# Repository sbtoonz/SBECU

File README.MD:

Original design sourced from https://github.com/dvjcodec/SCG-ECU-1.0
Teensy schematic sourced from PJRC

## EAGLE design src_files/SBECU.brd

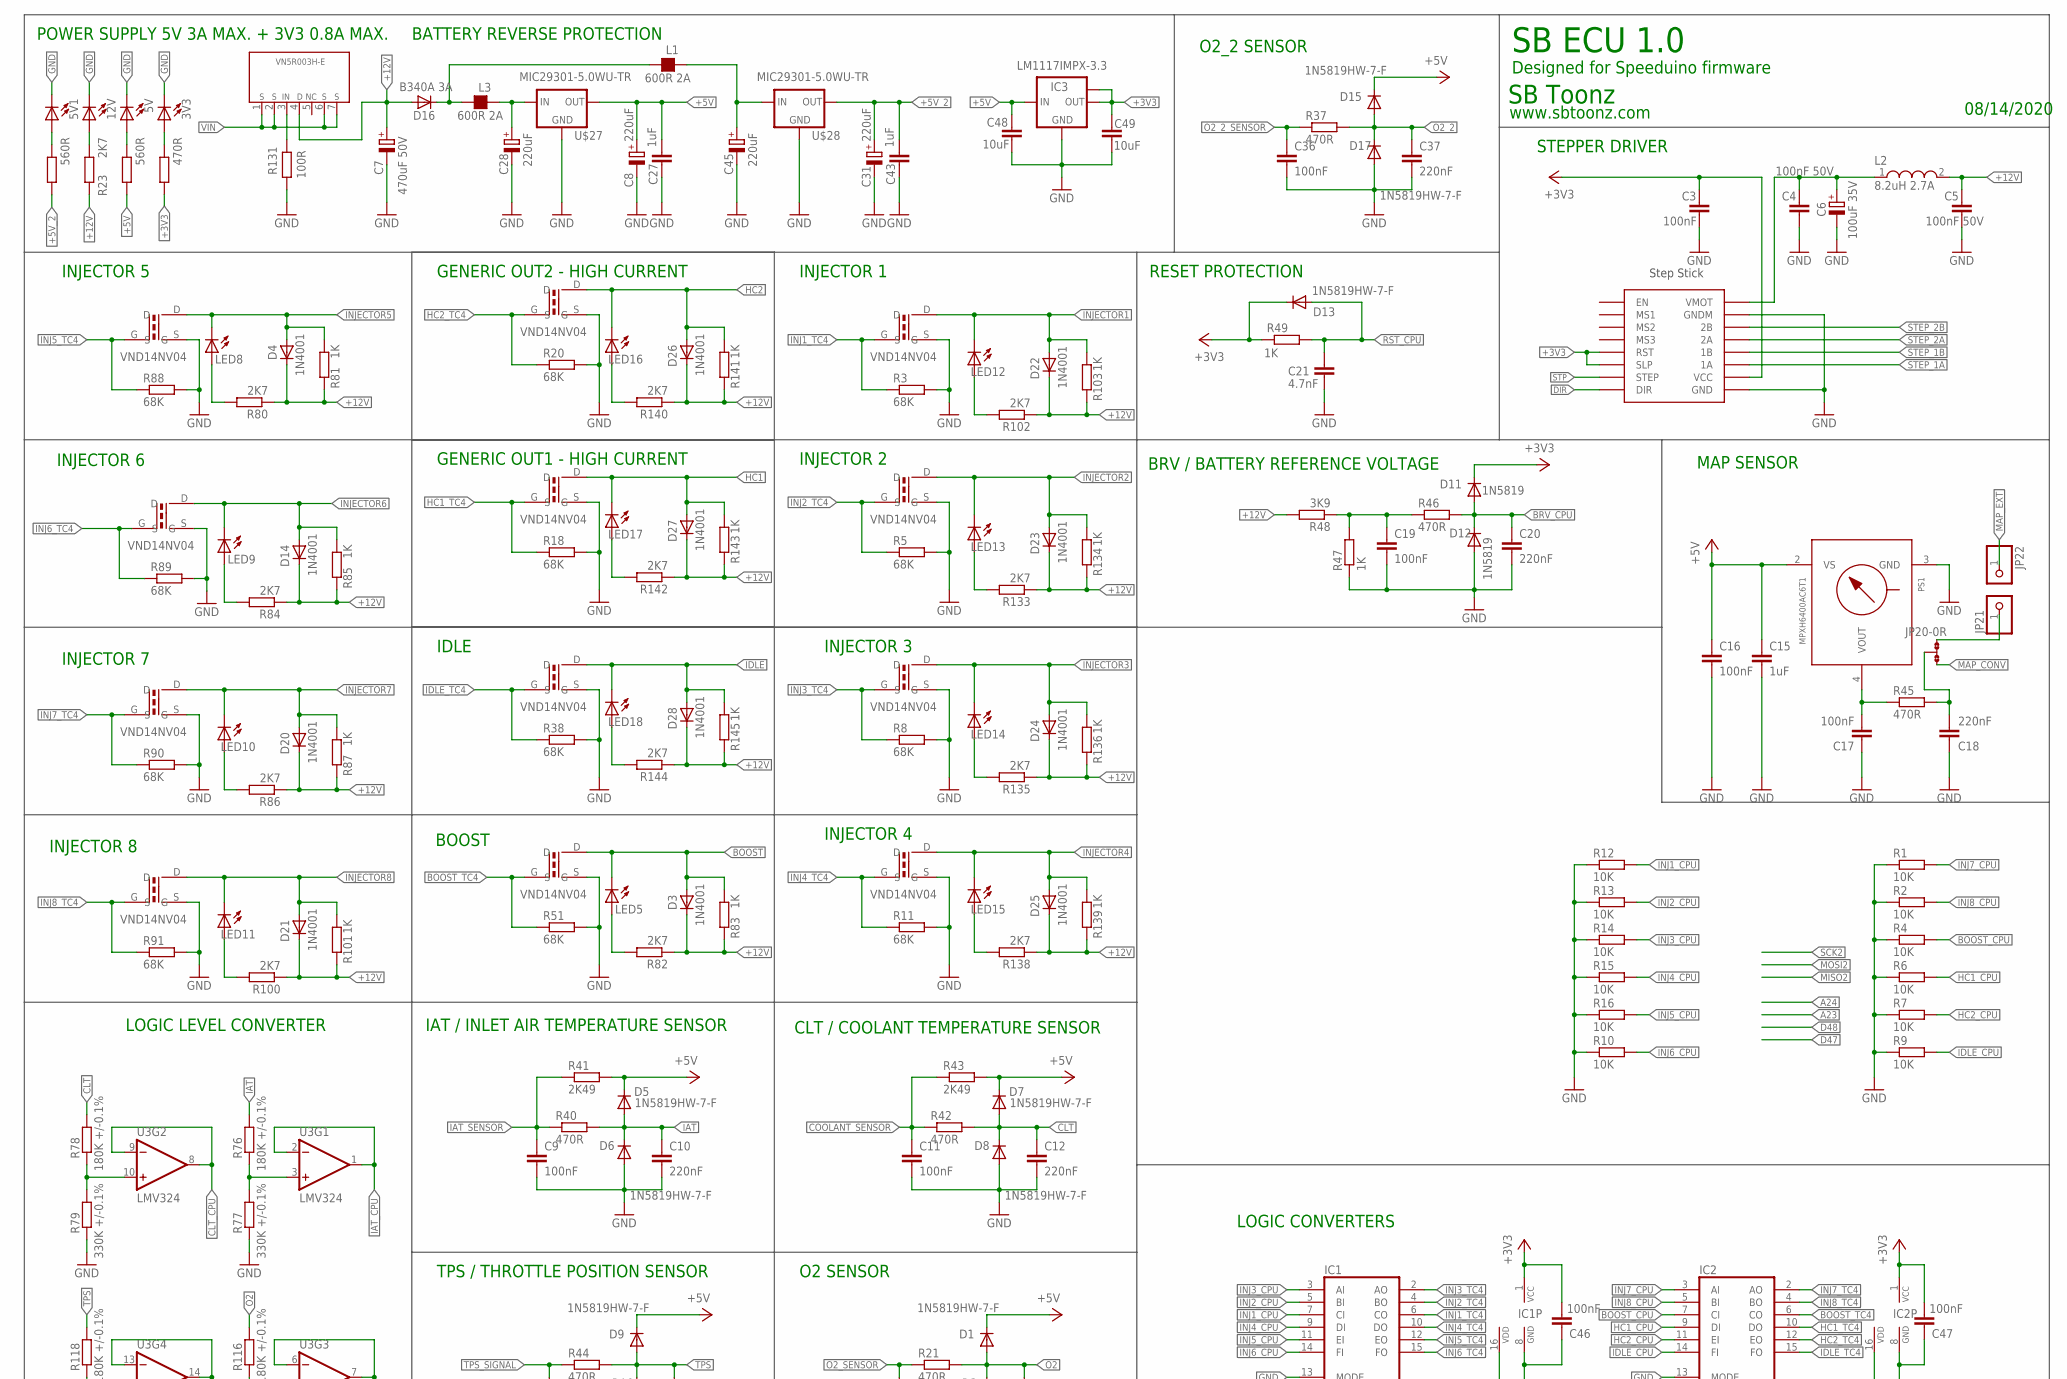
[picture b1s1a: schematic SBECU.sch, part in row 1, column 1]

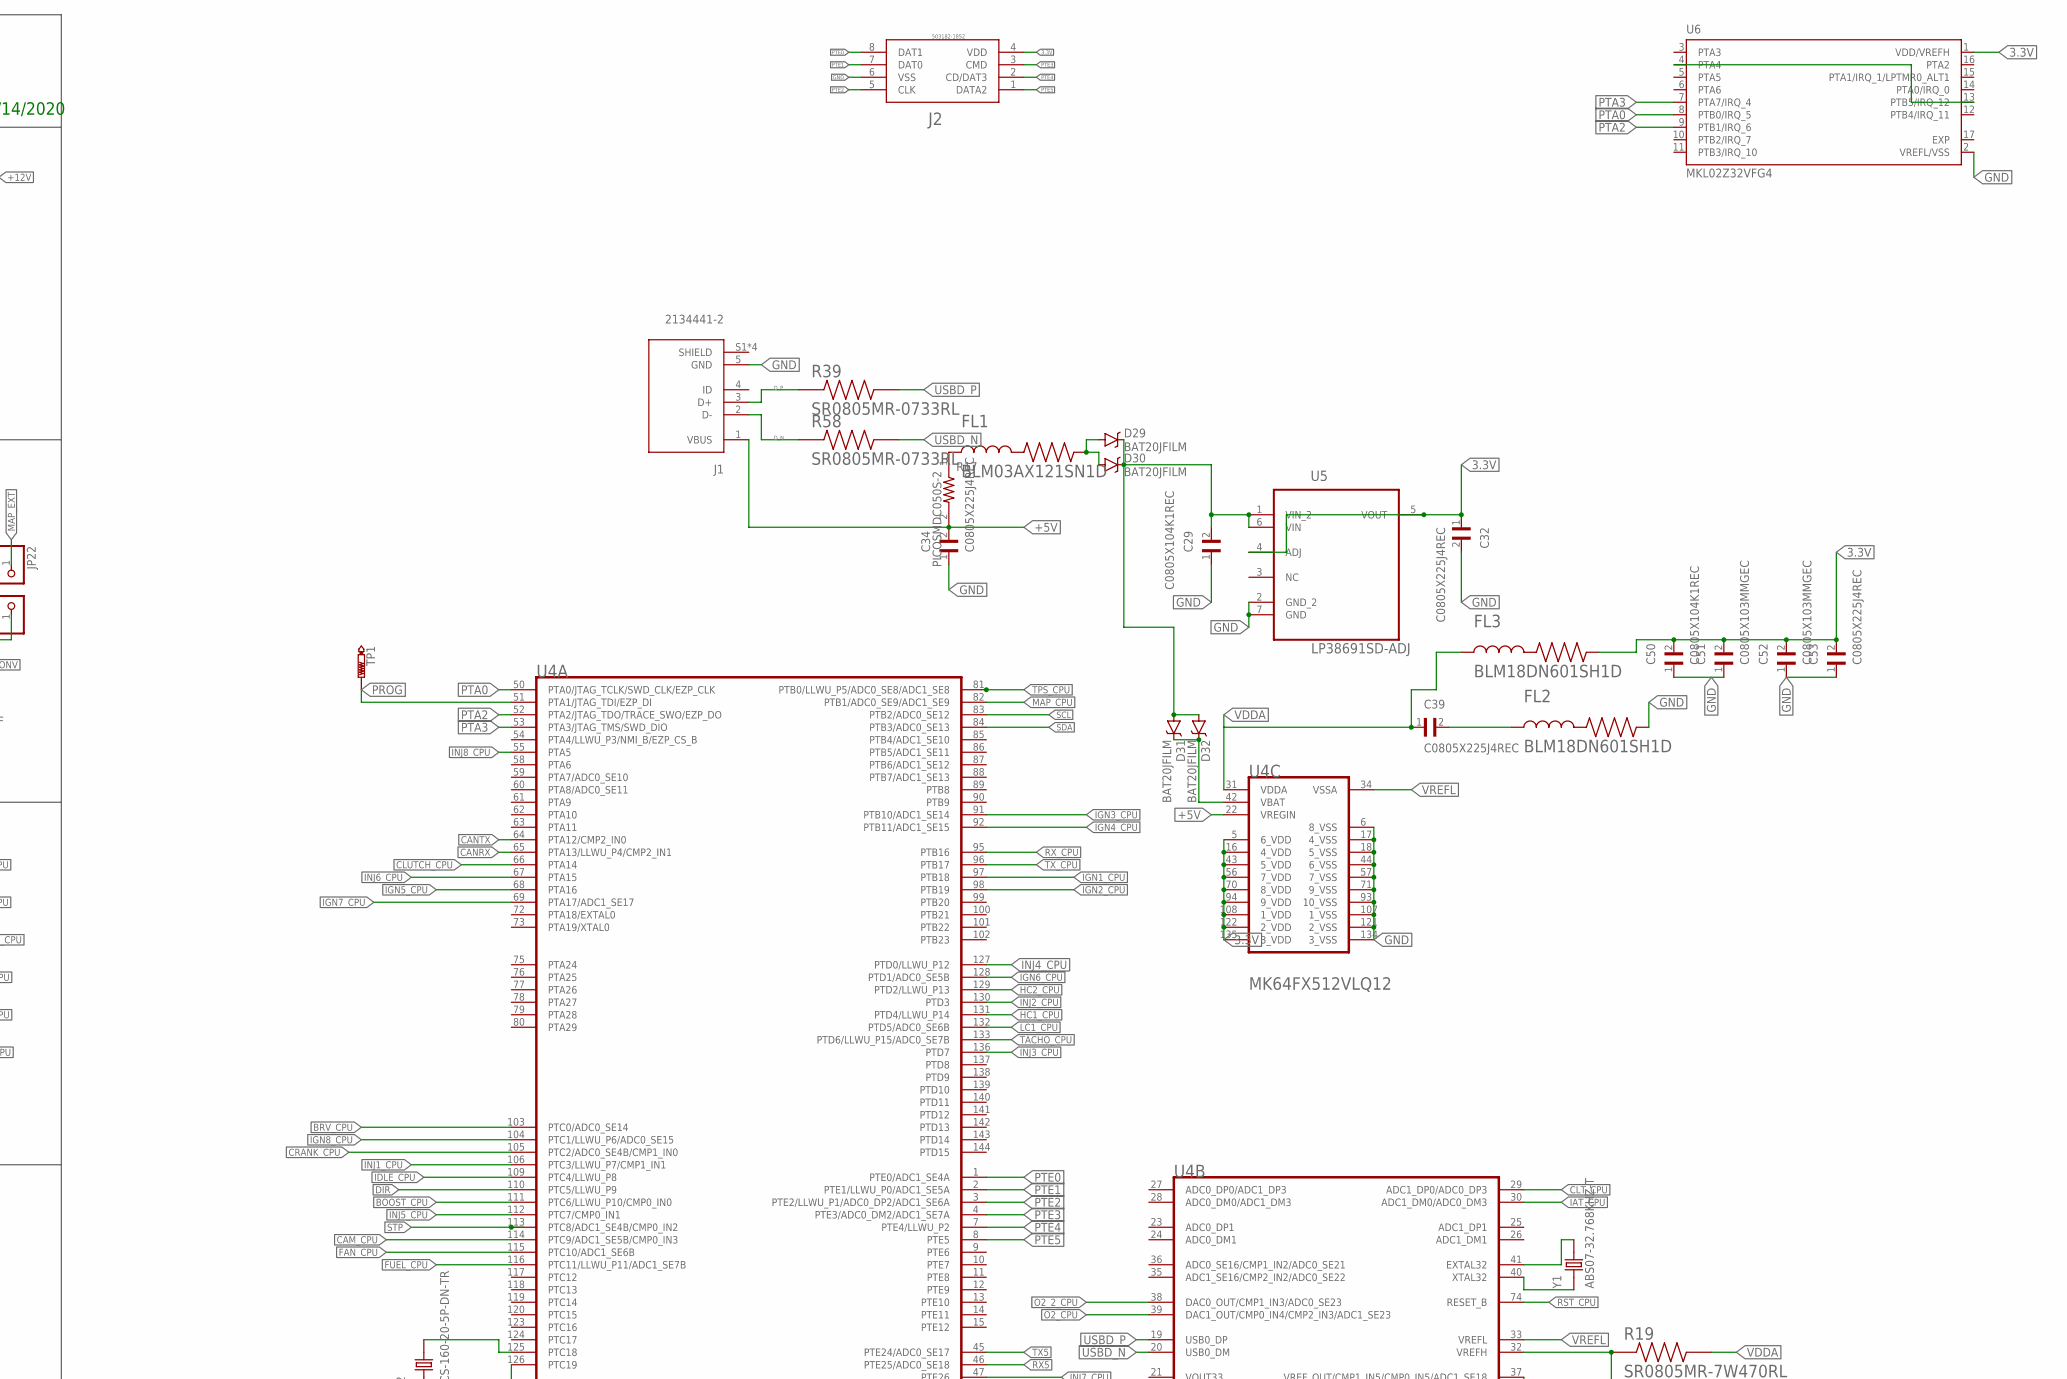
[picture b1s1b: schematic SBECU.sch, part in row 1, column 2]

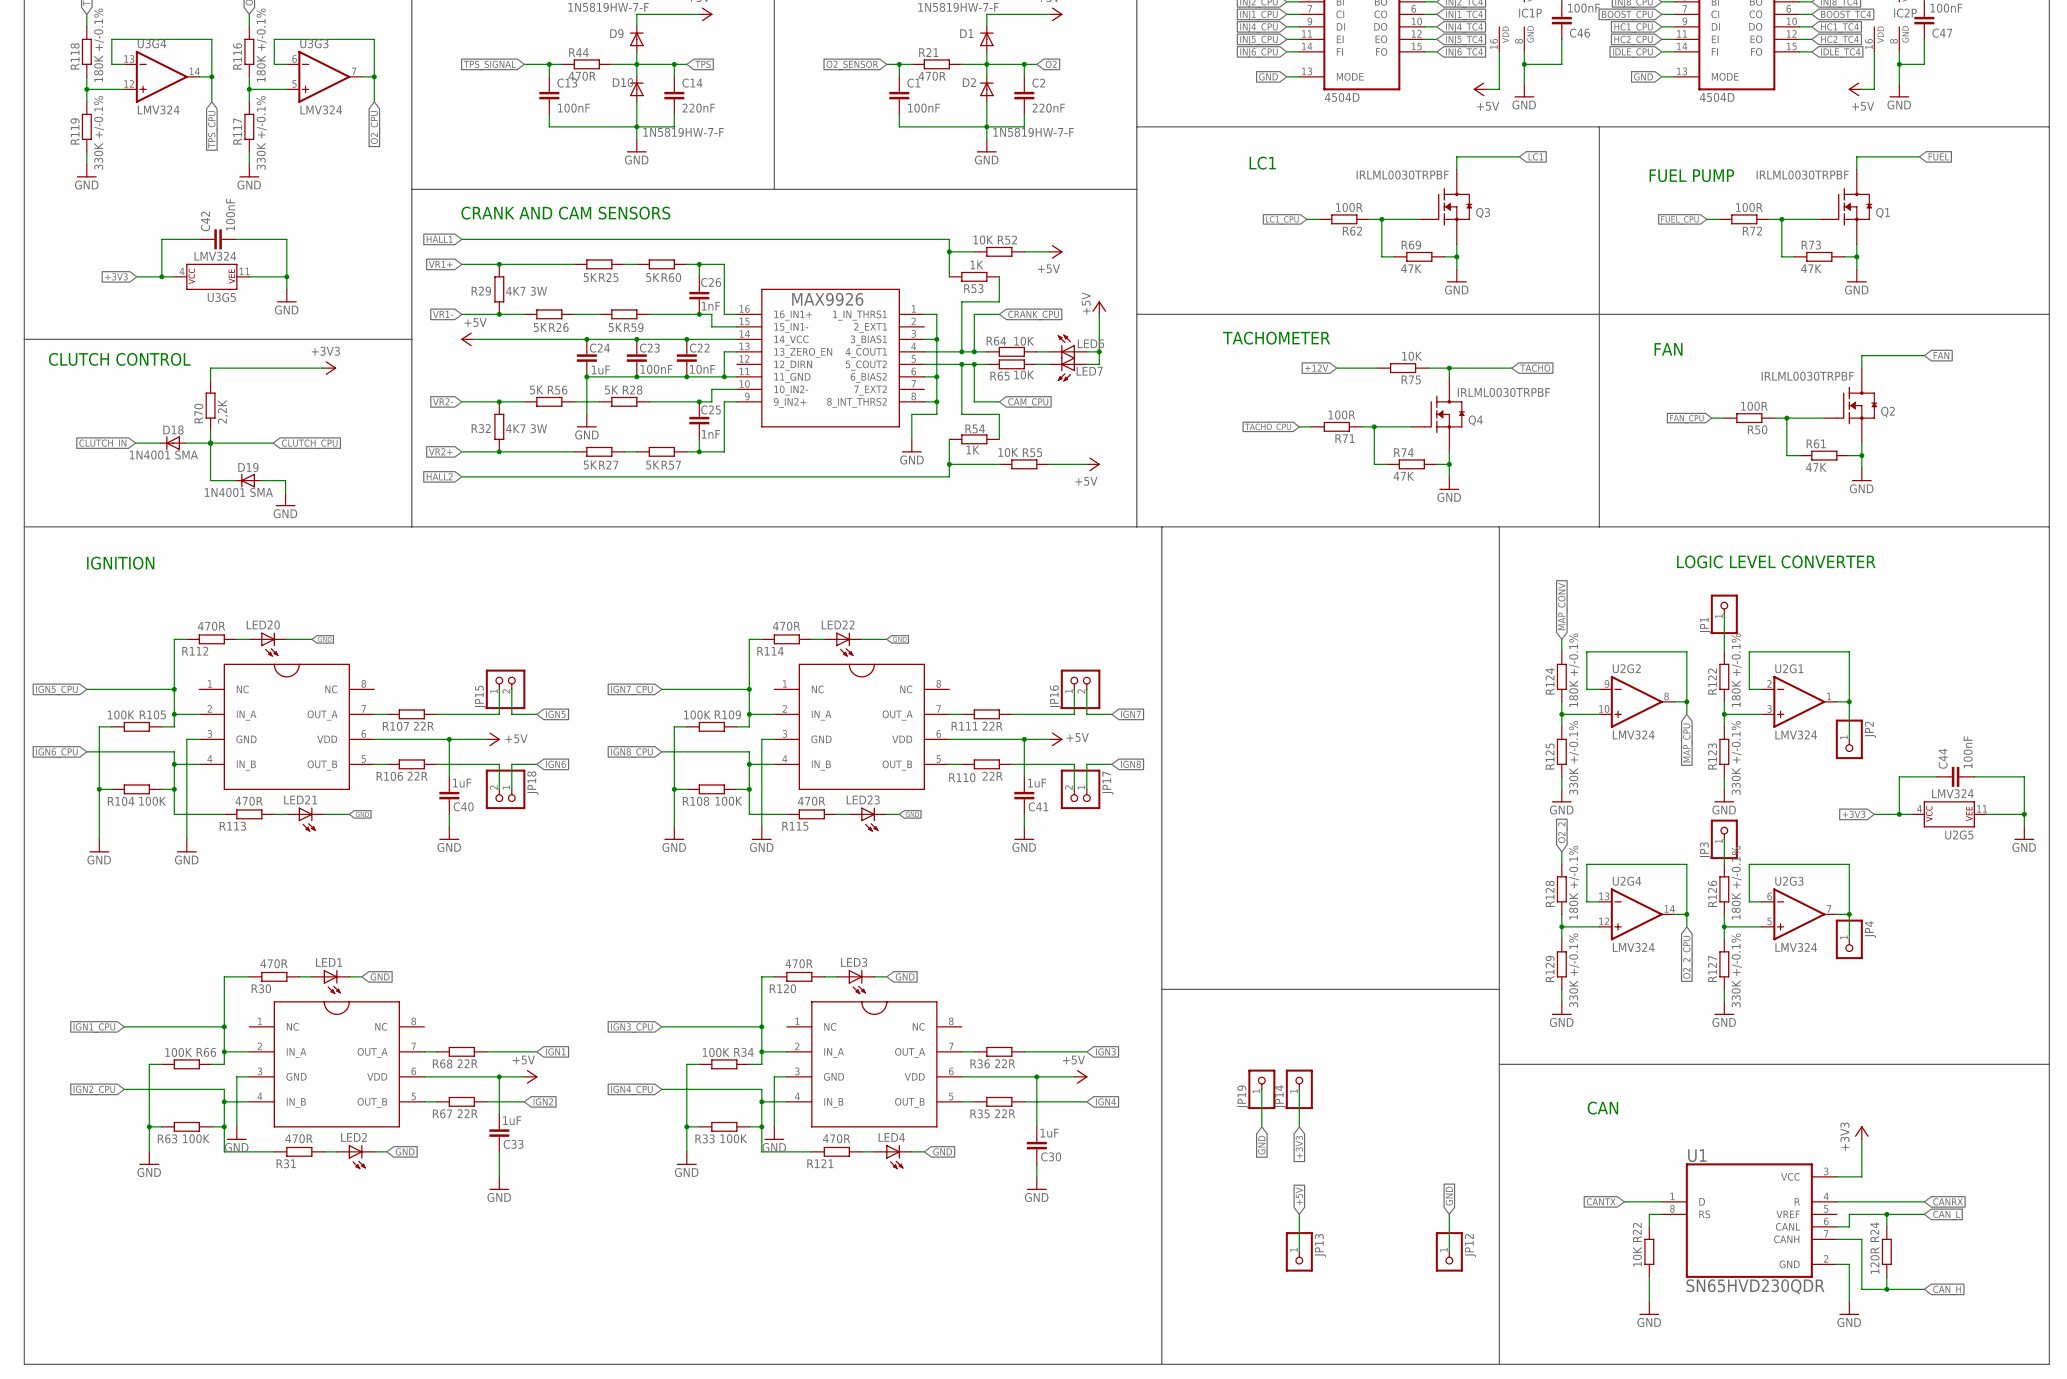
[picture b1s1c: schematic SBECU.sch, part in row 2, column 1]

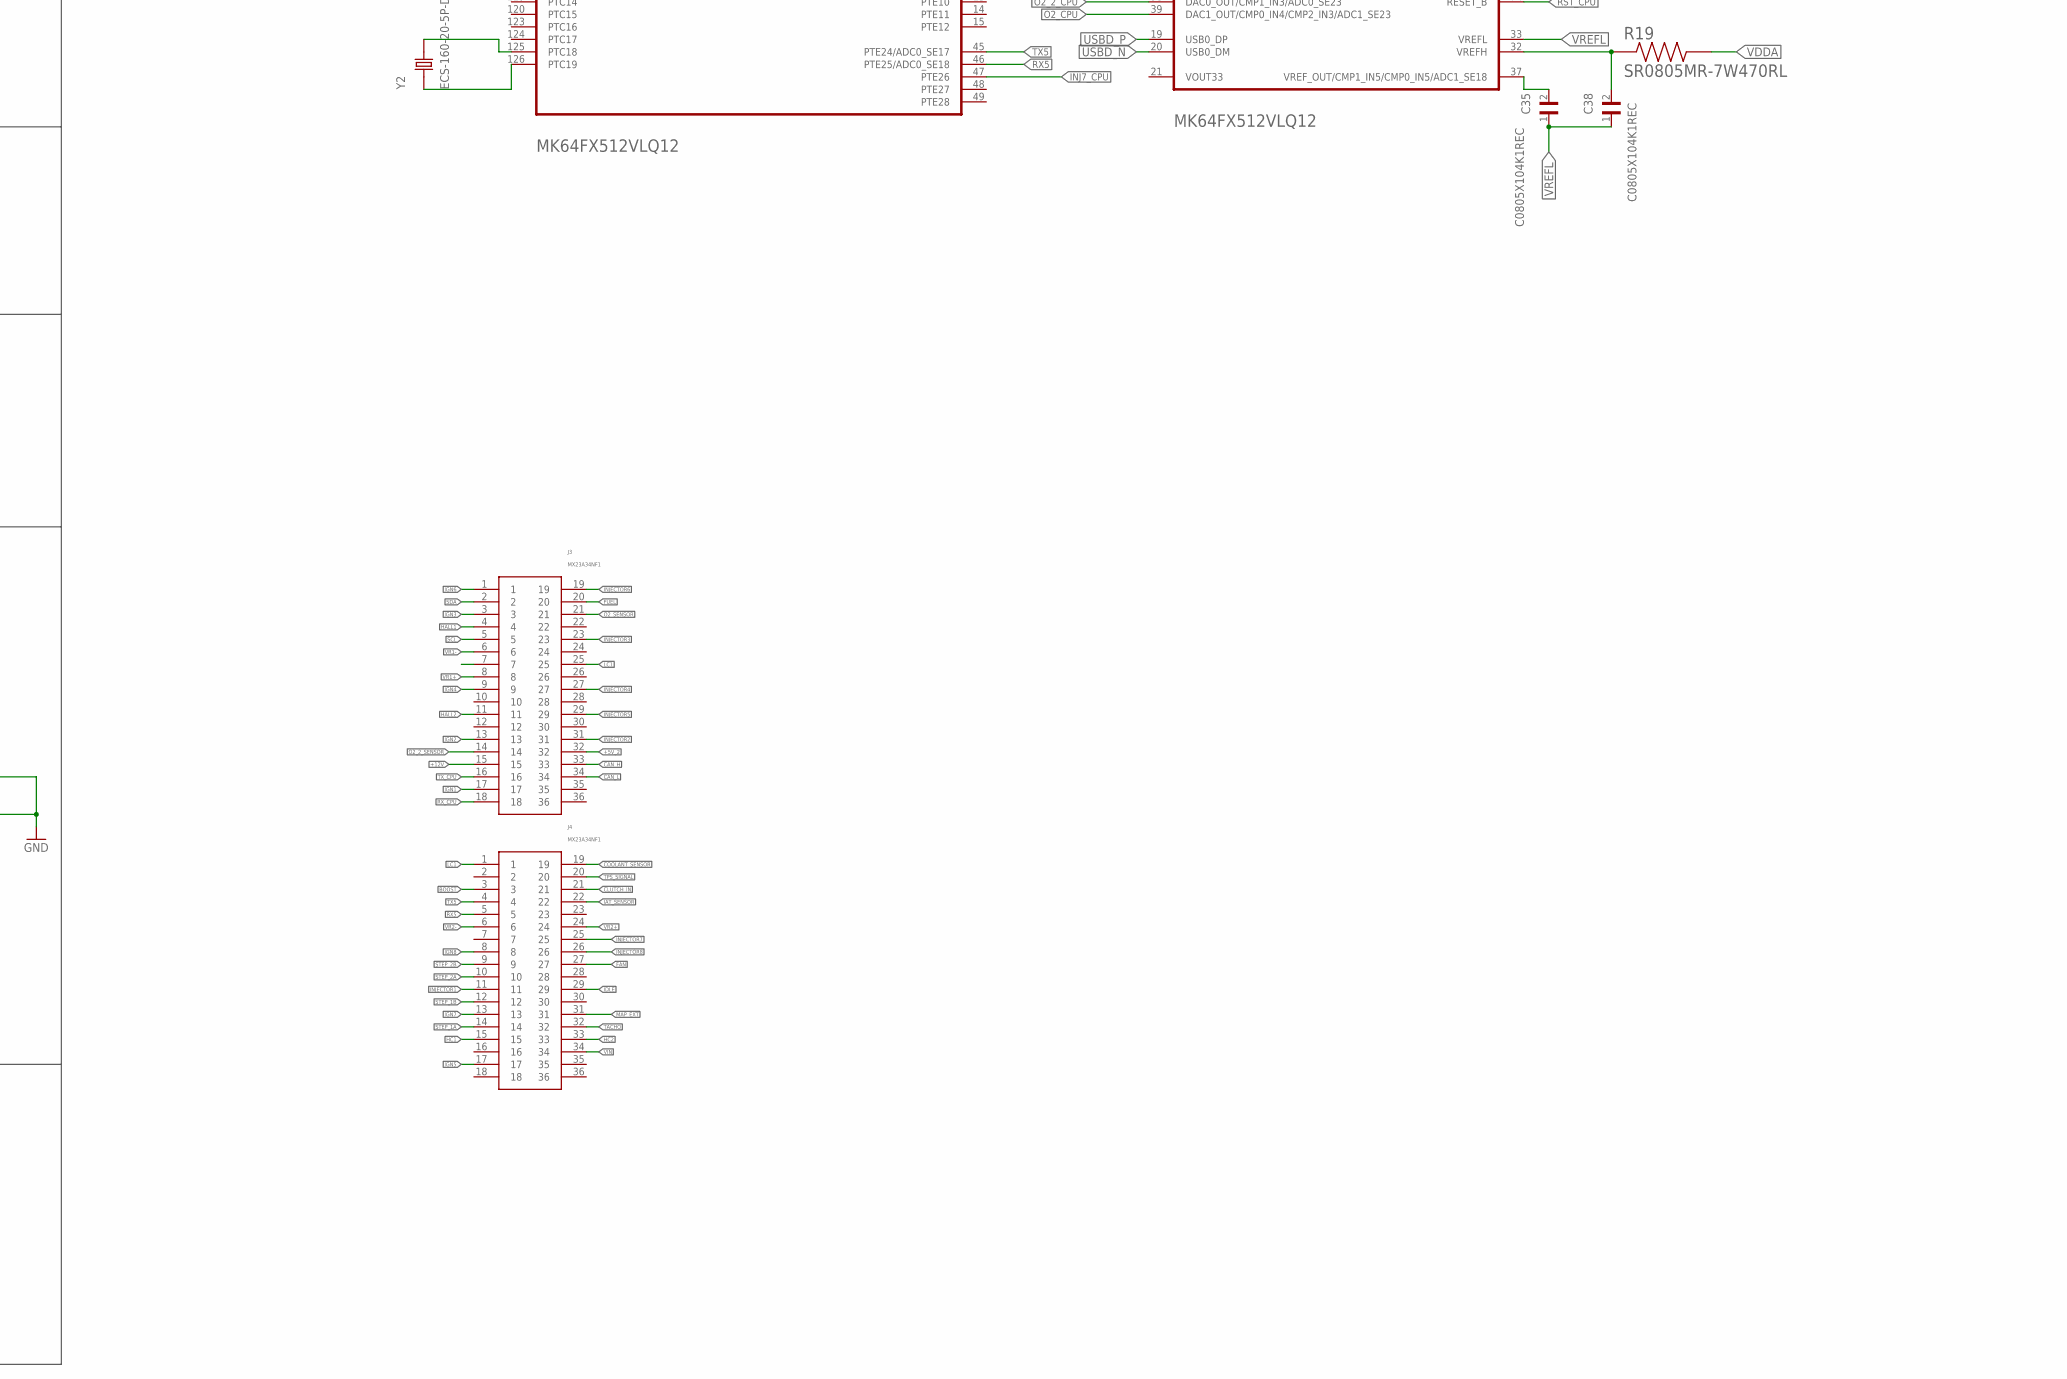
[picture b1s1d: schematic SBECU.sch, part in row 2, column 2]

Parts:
3V3, 5V, 5V1, 12V: LEDCHIP-LED0805; CHIP-LED0805
C1, C3, C9, C11, C13, C16, C17, C19, C23, C36, C42, C44, C46, C47: 100nF; C0805
C2, C10, C12, C14, C18, C20, C37: 220nF; C0805
C4, C5: 100nF 50V; C0805
C6: 100uF 35V; PANASONIC_D
C7: 470uF 50V; PANASONIC_G
C8, C28, C31, C45: 220uF; PANASONIC_D
C15, C24, C27, C30, C33, C40, C41, C43: 1uF; C0805
C21: 4.7nF; C0805
C22: 10nF; C0805
C25, C26: 1nF; C0805
C29, C35, C38, C50: C0805X104K1REC; CAPC2012X110N
C32, C34, C39, C53: C0805X225J4REC; CAPC2012X140N
C48, C49: 10uF; C0805
C51, C52: C0805X103MMGEC; CAPC2012X100N
D1, D2, D5, D6, D7, D8, D9, D10, D13, D15, D17: 1N5819HW-7-F; SOD123
D3, D4, D14, D20, D21, D22, D23, D24, D25, D26, D27, D28: 1N4001; D-2.5
D11, D12: 1N5819; SOD123
D16: B340A 3A; DO214AC
D18, D19: 1N4001 SMA; DO214AC
D29, D30, D31, D32: BAT20JFILM; SOD-323
FL1: BLM03AX121SN1D; BEADC0603X33N
FL2, FL3: BLM18DN601SH1D; BEADC1608X95N
IC1, IC2: 4504D; SO16
IC3: LM1117IMPX-3.3; SOT223
J1: 2134441-2; TE_2134441-2
J2: 503182-1852; 5031821852
J3, J4: MX23A34NF1
JP1, JP2, JP3, JP4, JP12, JP13, JP14, JP19, JP21, JP22: PINHD-1X1; 1X01
JP15, JP16, JP17, JP18: PINHD-1X2; 1X02
JP20: 0R-JUMPA; A0R-JMP
L1, L3: 600R 2A; L1206
L2: 8.2uH 2.7A; WE-PD_7332/7345_PLASTIC_BASE
LED1, LED2, LED3, LED4, LED6, LED7, LED20, LED21, LED22, LED23: LEDCHIP-LED0805; CHIP-LED0805
LED5, LED8, LED9, LED10, LED11, LED12, LED13, LED14, LED15, LED16, LED17, LED18: LEDCHIPLED_0805; CHIPLED_0805
PS1: MPXH6400AC6T1; 1317A
Q1, Q2, Q3, Q4: IRLML0030TRPBF; SOT95P280X135-3N
R1, R2, R4, R6, R7, R9, R10, R12, R13, R14, R15, R16, R22, R52, R55, R64, R65, R75: 10K; R0805
R3, R5, R8, R11, R18, R20, R38, R51, R88, R89, R90, R91: 68K; R0805
R17: PICOSMDC050S-2; RESC2012X65N
R19: SR0805MR-7W470RL; RESC2012X60N
R21, R30, R31, R37, R40, R42, R44, R45, R46, R112, R113, R114, R115, R120, R121, R137: 470R; R0805
R23, R80, R82, R84, R86, R100, R102, R133, R135, R138, R140, R142, R144: 2K7; R0805
R24: 120R; R0805
R25, R26, R27, R28, R56, R57, R59, R60: 5K; R0805
R29, R32: 4K7 3W; R2512
R33, R34, R63, R66, R104, R105, R108, R109: 100K; R0805
R35, R36, R67, R68, R106, R107, R110, R111: 22R; M1206
R39, R58: SR0805MR-0733RL; RESC2012X60N
R41, R43: 2K49; R0805
R47, R49, R53, R54, R81, R83, R85, R87, R101, R103, R134, R136, R139, R141, R143, R145: 1K; R0805
R48: 3K9; R0805
R50, R62, R71, R72, R131: 100R; R0805
R61, R69, R73, R74: 47K; R0805
R70: 2,2K; R0805
R76, R78, R116, R118, R122, R124, R126, R128: 180K +/-0.1%; R0805
R77, R79, R117, R119, R123, R125, R127, R129: 330K +/-0.1%; R0805
R130, R132: 560R; R0805
STEPSTICK-X: STEP-STICK
TP1: PTR1PAD1-13; P1-13
U1: SN65HVD230QDR; SOIC127P600X175-8N
U2, U3: LMV324; SO14
U4: FREESCALE_SEMICONDUCTOR_MK64FX512VLQ12FREESCALE_S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; FREESCALE_SEMICONDUCTOR_MK64FX512VLQ12_0
U5: LP38691SD-ADJ; DFN300X300X80-7N
U6: MKL02Z32VFG4; QFN50P300X300X65-17N
U$2, U$3, U$4, U$5, U$6, U$8, U$12, U$13, U$19, U$20, U$21, U$22: DPAK_N-CHANNEL_MOSFET
U$9, U$11, U$25, U$26: TC427SO-8; SO-8
U$10: MAX9926; QSOP16
U$18: VN5R003H-E; VN5R003H-E_HPAK_TO267_7
U$27, U$28: MIC29301-5.0WU-TR; TO263-3
Y1: ABS07-32.768KHZ-T; XTAL_ABS07-32.768KHZ-T
Y2: ECS-160-20-5P-DN-TR; XTAL_ECS-160-20-5P-DN-TR

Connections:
3.3V: C32.1, C50.2, C51.2, C52.2, C53.2, FL3.2, J2.4 (VDD), U4.5 (6_VDD), U4.16 (4_VDD), U4.43 (5_VDD), U4.56 (7_VDD), U4.70 (8_VDD), U4.94 (9_VDD), U4.108 (1_VDD), U4.122 (2_VDD), U4.135 (3_VDD), U5.4 (ADJ), U5.5 (VOUT), U6.1 (VDD/VREFH)
+3V3: C3.1, C42.1, C44.1, C46.2, C47.2, C49.1, D11.C, D13.C, IC1.1 (VCC), IC2.1 (VCC), IC3.2 (OUT), IC3.TAB (OUT1), JP14.1, R49.1, R70.2, R137.2, STEPSTICK-X.RST, STEPSTICK-X.SLP, STEPSTICK-X.VCC, U1.3 (VCC), U2.4 (P$V+), U3.4 (P$V+)
+5V: C8.+, C15.1, C16.1, C22.1, C23.1, C24.1, C27.1, C30.2, C33.2, C34.2, C40.2, C41.2, C48.1, D1.C, D5.C, D7.C, D9.C, D15.C, IC1.16 (VDD), IC2.16 (VDD), IC3.3 (IN), J1.1 (VBUS), JP13.1, LED6.A, LED7.A, PS1.2 (VS), R17.2, R41.2, R43.2, R52.1, R55.1, R130.2, U4.22 (VREGIN), U$9.6 (VDD), U$10.14 (14_VCC), U$11.6 (VDD), U$25.6 (VDD), U$26.6 (VDD), U$27.3 (OUT)
+5V_2: C31.+, C43.1, J3.32, R132.2, U$28.3 (OUT)
+12V: C5.1, C7.+, D3.C, D4.C, D14.C, D16.A, D20.C, D21.C, D22.C, D23.C, D24.C, D25.C, D26.C, D27.C, D28.C, J3.15, L2.2, R23.2, R48.2, R75.2, R80.1, R81.1, R82.1, R83.1, R84.1, R85.1, R86.1, R87.1, R100.1, R101.1, R102.1, R103.1, R133.1, R134.1, R135.1, R136.1, R138.1, R139.1, R140.1, R141.1, R142.1, R143.1, R144.1, R145.1, U$18.4
BOOST: D3.A, J4.3, LED5.C, R83.2, U$13.D
BOOST_CPU: IC2.7 (CI), R4.2, U4.111 (PTC6/LLWU_P10/CMP0_IN0)
BOOST_TC4: IC2.6 (CO), R51.1, U$13.G
BRV_CPU: C20.1, D11.A, D12.C, R46.2, U4.103 (PTC0/ADC0_SE14)
CAM_CPU: R54.1, R65.1, U4.114 (PTC9/ADC1_SE5B/CMP0_IN3), U$10.5 (5_COUT2)
CANRX: U1.4 (R), U4.65 (PTA13/LLWU_P4/CMP2_IN1)
CANTX: U1.1 (D), U4.64 (PTA12/CMP2_IN0)
CAN_H: J3.33, R24.2, U1.7 (CANH)
CAN_L: J3.34, R24.1, U1.6 (CANL)
CLT: C12.1, D7.A, D8.C, R42.2, R78.2
CLT_CPU: U3.8 (OUT), U3.9 (-IN), U4.29 (ADC1_DP0/ADC0_DP3)
CLUTCH_CPU: D18.A, D19.C, R70.1, U4.66 (PTA14)
CLUTCH_IN: D18.C, J4.21
COOLANT_SENSOR: C11.1, J4.19, R42.1, R43.1
CRANK_CPU: R53.2, R64.1, U4.105 (PTC2/ADC0_SE4B/CMP1_IN0), U$10.4 (4_COUT1)
DIR: STEPSTICK-X.DIR, U4.110 (PTC5/LLWU_P9)
D_N: J1.2 (D-), R58.1
D_P: J1.3 (D+), R39.1
EXP: U6.17 (EXP)
FAN: J4.27, Q2.3 (D)
FAN_CPU: R50.2, U4.115 (PTC10/ADC1_SE6B)
FUEL: J3.20, Q1.3 (D)
FUEL_CPU: R72.2, U4.116 (PTC11/LLWU_P11/ADC1_SE7B)
GND: 3V3.C, 5V.C, 5V1.C, 12V.C, C1.2, C2.2, C3.2, C4.2, C5.2, C6.-, C7.-, C8.-, C9.2, C10.2, C11.2, C12.2, C13.2, C14.2, C15.2, C16.2, C17.1, C18.1, C19.2, C20.2, C21.2, C22.2, C23.2, C24.2, C27.2, C28.-, C29.1, C30.1, C31.-, C32.2, C33.1, C34.1, C36.2, C37.2, C40.1, C41.1, C42.2, C43.2, C44.2, C45.-, C46.1, C47.1, C48.2, C49.2, C50.1, C51.1, C52.1, C53.1, D2.A, D6.A, D8.A, D10.A, D12.A, D17.A, D19.A, FL2.2, IC1.8 (GND), IC1.13 (MODE), IC2.8 (GND), IC2.13 (MODE), IC3.1 (GND), J1.5 (GND), J2.6 (VSS), JP12.1, JP19.1, LED1.C, LED2.C, LED3.C, LED4.C, LED20.C, LED21.C, LED22.C, LED23.C, PS1.3 (GND), Q1.2 (S), Q2.2 (S), Q3.2 (S), Q4.2 (S), R1.1, R2.1, R3.2, R4.1, R5.2, R6.1, R7.1, R8.2, R9.1, R10.1, R11.2, R12.1, R13.1, R14.1, R15.1, R16.1, R18.2, R20.2, R22.2, R33.1, R34.2, R38.2, R47.1, R51.2, R61.2, R63.1, R66.2, R69.2, R73.2, R74.2, R77.1, R79.1, R88.2, R89.2, R90.2, R91.2, R104.1, R105.2, R108.1, R109.2, R117.1, R119.1, R123.1, R125.1, R127.1, R129.1, R131.1, STEPSTICK-X.GND, STEPSTICK-X.GNDM, U1.2 (GND), U2.11 (P$V-), U3.11 (P$V-), U4.6 (8_VSS), U4.17 (4_VSS), U4.18 (5_VSS), U4.44 (6_VSS), U4.57 (7_VSS), U4.71 (9_VSS), U4.93 (10_VSS), U4.107 (1_VSS), U4.121 (2_VSS), U4.134 (3_VSS), U5.2 (GND_2), U5.7 (GND), U6.2 (VREFL/VSS), U$2.S, U$3.S, U$4.S, U$5.S, U$6.S, U$8.S, U$9.3 (GND), U$10.1 (1_IN_THRS1), U$10.3 (3_BIAS1), U$10.6 (6_BIAS2), U$10.8 (8_INT_THRS2), U$10.11 (11_GND), U$10.13 (13_ZERO_EN), U$11.3 (GND), U$12.S, U$13.S, U$19.S, U$20.S, U$21.S, U$22.S, U$25.3 (GND), U$26.3 (GND), U$27.TAB (GND), U$28.TAB (GND)
HALL1: J3.4, R52.2, R53.1
HALL2: J3.11, R54.2, R55.2
HC1: D27.A, J4.15, LED17.C, R143.2, U$3.D
HC1_CPU: IC2.9 (DI), R6.2, U4.131 (PTD4/LLWU_P14)
HC1_TC4: IC2.10 (DO), R18.1, U$3.G
HC2: D26.A, J4.33, LED16.C, R141.2, U$2.D
HC2_CPU: IC2.11 (EI), R7.2, U4.129 (PTD2/LLWU_P13)
HC2_TC4: IC2.12 (EO), R20.1, U$2.G
IAT: C10.1, D5.A, D6.C, R40.2, R76.2
IAT_CPU: U3.1 (OUT), U3.2 (-IN), U4.30 (ADC1_DM0/ADC0_DM3)
IAT_SENSOR: C9.1, J4.22, R40.1, R41.1
IDLE: D28.A, J4.29, LED18.C, R145.2, U$5.D
IDLE_CPU: IC2.14 (FI), R9.2, U4.109 (PTC4/LLWU_P8)
IDLE_TC4: IC2.15 (FO), R38.1, U$5.G
IGN1: J3.17, R68.2
IGN1_CPU: R30.2, R66.1, U4.97 (PTB18), U$9.2 (IN_A)
IGN2: J3.13, R67.2
IGN2_CPU: R31.2, R63.2, U4.98 (PTB19), U$9.4 (IN_B)
IGN3: J3.3, R36.2
IGN3_CPU: R34.1, R120.2, U4.91 (PTB10/ADC1_SE14), U$11.2 (IN_A)
IGN4: J3.9, R35.2
IGN4_CPU: R33.2, R121.2, U4.92 (PTB11/ADC1_SE15), U$11.4 (IN_B)
IGN5: J4.17, JP15.2
IGN5_CPU: R105.1, R112.2, U4.68 (PTA16), U$25.2 (IN_A)
IGN6: J3.1, JP18.1
IGN6_CPU: R104.2, R113.2, U4.128 (PTD1/ADC0_SE5B), U$25.4 (IN_B)
IGN7: J4.13, JP16.2
IGN7_CPU: R109.1, R114.2, U4.69 (PTA17/ADC1_SE17), U$26.2 (IN_A)
IGN8: J4.8, JP17.1
IGN8_CPU: R108.2, R115.2, U4.104 (PTC1/LLWU_P6/ADC0_SE15), U$26.4 (IN_B)
INJ1_CPU: IC1.7 (CI), R12.2, U4.106 (PTC3/LLWU_P7/CMP1_IN1)
INJ1_TC4: IC1.6 (CO), R3.1, U$12.G
INJ2_CPU: IC1.5 (BI), R13.2, U4.130 (PTD3)
INJ2_TC4: IC1.4 (BO), R5.1, U$4.G
INJ3_CPU: IC1.3 (AI), R14.2, U4.136 (PTD7)
INJ3_TC4: IC1.2 (AO), R8.1, U$6.G
INJ4_CPU: IC1.9 (DI), R15.2, U4.127 (PTD0/LLWU_P12)
INJ4_TC4: IC1.10 (DO), R11.1, U$8.G
INJ5_CPU: IC1.11 (EI), R16.2, U4.112 (PTC7/CMP0_IN1)
INJ5_TC4: IC1.12 (EO), R88.1, U$19.G
INJ6_CPU: IC1.14 (FI), R10.2, U4.67 (PTA15)
INJ6_TC4: IC1.15 (FO), R89.1, U$20.G
INJ7_CPU: IC2.3 (AI), R1.2, U4.47 (PTE26)
INJ7_TC4: IC2.2 (AO), R90.1, U$21.G
INJ8_CPU: IC2.5 (BI), R2.2, U4.55 (PTA5)
INJ8_TC4: IC2.4 (BO), R91.1, U$22.G
INJECTOR1: D22.A, J4.11, LED12.C, R103.2, U$12.D
INJECTOR2: D23.A, J3.31, LED13.C, R134.2, U$4.D
INJECTOR3: D24.A, J3.23, LED14.C, R136.2, U$6.D
INJECTOR4: D25.A, J3.27, LED15.C, R139.2, U$8.D
INJECTOR5: D4.A, J3.29, LED8.C, R81.2, U$19.D
INJECTOR6: D14.A, J3.19, LED9.C, R85.2, U$20.D
INJECTOR7: D20.A, J4.25, LED10.C, R87.2, U$21.D
INJECTOR8: D21.A, J4.26, LED11.C, R101.2, U$22.D
LC1: J3.25, J4.1, Q3.3 (D)
LC1_CPU: R62.2, U4.132 (PTD5/ADC0_SE6B)
MAP_CONV: JP20.1, R124.2
MAP_CPU: U2.8 (OUT), U2.9 (-IN), U4.82 (PTB1/ADC0_SE9/ADC1_SE9)
MAP_EXT: J4.31, JP22.1
unnamed: LED8.A, R80.2
unnamed: LED5.A, R82.2
unnamed: R67.1, U$9.5 (OUT_B)
unnamed: R68.1, U$9.7 (OUT_A)
unnamed: R35.1, U$11.5 (OUT_B)
unnamed: R36.1, U$11.7 (OUT_A)
unnamed: Q2.1 (G), R50.1, R61.1
unnamed: Q3.1 (G), R62.1, R69.1
unnamed: R22.1, U1.8 (RS)
unnamed: R78.1, R79.2, U3.10 (+IN)
unnamed: R76.1, R77.2, U3.3 (+IN)
unnamed: LED1.A, R30.1
unnamed: R116.1, R117.2, U3.5 (+IN)
unnamed: LED9.A, R84.2
unnamed: C4.1, C6.+, L2.1, STEPSTICK-X.VMOT
unnamed: LED11.A, R100.2
unnamed: LED15.A, R138.2
unnamed: LED10.A, R86.2
unnamed: LED2.A, R31.1
unnamed: C19.1, R46.1, R47.2, R48.1
unnamed: Q4.1 (G), R71.1, R74.1
unnamed: LED12.A, R102.2
unnamed: C17.2, PS1.4 (VOUT), R45.1
unnamed: LED16.A, R140.2
unnamed: C25.2, R57.1, U$10.9 (9_IN2+)
unnamed: C26.1, R60.1, U$10.16 (16_IN1+)
unnamed: C26.2, R59.1, U$10.15 (15_IN1-)
unnamed: C25.1, R28.1, U$10.10 (10_IN2-)
unnamed: R106.1, U$25.5 (OUT_B)
unnamed: R107.1, U$25.7 (OUT_A)
unnamed: R25.1, R60.2
unnamed: R110.1, U$26.5 (OUT_B)
unnamed: R111.1, U$26.7 (OUT_A)
unnamed: LED20.A, R112.1
unnamed: LED21.A, R113.1
unnamed: LED22.A, R114.1
unnamed: LED23.A, R115.1
unnamed: LED7.C, R65.2
unnamed: LED6.C, R64.2
unnamed: 12V.A, R23.1
unnamed: 5V.A, R130.1
unnamed: R26.1, R59.2
unnamed: R27.1, R57.2
unnamed: R28.2, R56.1
unnamed: R122.1, R123.2, U2.3 (+IN)
unnamed: R118.1, R119.2, U3.12 (+IN)
unnamed: R124.1, R125.2, U2.10 (+IN)
unnamed: R126.1, R127.2, U2.5 (+IN)
unnamed: R128.1, R129.2, U2.12 (+IN)
unnamed: JP1.1, R122.2
unnamed: JP2.1, U2.1 (OUT), U2.2 (-IN)
unnamed: JP3.1, R126.2
unnamed: JP4.1, U2.6 (-IN), U2.7 (OUT)
unnamed: LED3.A, R120.1
unnamed: LED4.A, R121.1
unnamed: R131.2, U$18.3
unnamed: D16.C, L1.2, L3.2
unnamed: C45.+, L1.1, U$28.1 (IN)
unnamed: 5V1.A, R132.1
unnamed: C28.+, L3.1, U$27.1 (IN)
unnamed: LED13.A, R133.2
unnamed: 3V3.A, R137.1
unnamed: LED14.A, R135.2
unnamed: LED17.A, R142.2
unnamed: LED18.A, R144.2
unnamed: Q1.1 (G), R72.1, R73.1
unnamed: JP15.1, R107.2
unnamed: JP16.1, R111.2
unnamed: JP18.2, R106.2
unnamed: JP17.2, R110.2
unnamed: JP20.3, JP21.1
unnamed: C18.2, JP20.2, R45.2
unnamed: FL1.1, R17.1
unnamed: D31.C, D32.C, U4.42 (VBAT)
unnamed: C29.2, D29.C, D30.C, D31.A, D32.A, U5.1 (VIN_2), U5.6 (VIN)
unnamed: D29.A, D30.A, FL1.2
unnamed: C35.2, U4.37 (VREF_OUT/CMP1_IN5/CMP0_IN5/ADC1_SE18)
unnamed: C38.2, R19.1, U4.32 (VREFH)
unnamed: C39.2, FL2.1
unnamed: U6.4 (PTA4), U6.13 (PTB5/IRQ_12)
unnamed: U4.40 (XTAL32), Y1.1
unnamed: U4.41 (EXTAL32), Y1.2
unnamed: U4.125 (PTC18), Y2.2
unnamed: U4.126 (PTC19), Y2.1
O2: C2.1, D1.A, D2.C, R21.2, R116.2
O2_2: C37.1, D15.A, D17.C, R37.2, R128.2
O2_2_CPU: U2.13 (-IN), U2.14 (OUT), U4.38 (DAC0_OUT/CMP1_IN3/ADC0_SE23)
O2_2_SENSOR: C36.1, J3.14, R37.1
O2_CPU: U3.6 (-IN), U3.7 (OUT), U4.39 (DAC1_OUT/CMP0_IN4/CMP2_IN3/ADC1_SE23)
O2_SENSOR: C1.1, J3.21, R21.1
PROG: TP1.TP, U4.51 (PTA1/JTAG_TDI/EZP_DI)
PTA0: U4.50 (PTA0/JTAG_TCLK/SWD_CLK/EZP_CLK), U6.8 (PTB0/IRQ_5)
PTA2: U4.52 (PTA2/JTAG_TDO/TRACE_SWO/EZP_DO), U6.9 (PTB1/IRQ_6)
PTA3: U4.53 (PTA3/JTAG_TMS/SWD_DIO), U6.7 (PTA7/IRQ_4)
PTE0: J2.8 (DAT1), U4.1 (PTE0/ADC1_SE4A)
PTE1: J2.7 (DAT0), U4.2 (PTE1/LLWU_P0/ADC1_SE5A)
PTE2: J2.5 (CLK), U4.3 (PTE2/LLWU_P1/ADC0_DP2/ADC1_SE6A)
PTE3: J2.3 (CMD), U4.4 (PTE3/ADC0_DM2/ADC1_SE7A)
PTE4: J2.2 (CD/DAT3), U4.7 (PTE4/LLWU_P2)
PTE5: J2.1 (DATA2), U4.8 (PTE5)
RST_CPU: C21.1, D13.A, R49.2, U4.74 (RESET_B)
RX5: J4.5, U4.46 (PTE25/ADC0_SE18)
RX_CPU: J3.18, U4.95 (PTB16)
SCL: J3.5, U4.83 (PTB2/ADC0_SE12)
SDA: J3.2, U4.84 (PTB3/ADC0_SE13)
SHIELD: J1.S1 (SHIELD), J1.S2 (SHIELD), J1.S3 (SHIELD), J1.S4 (SHIELD)
STEP_1A: J4.14, STEPSTICK-X.1A
STEP_1B: J4.12, STEPSTICK-X.1B
STEP_2A: J4.10, STEPSTICK-X.2A
STEP_2B: J4.9, STEPSTICK-X.2B
STP: STEPSTICK-X.SPT (STEP), U4.113 (PTC8/ADC1_SE4B/CMP0_IN2)
TACHO: J4.32, Q4.3 (D), R75.1
TACHO_CPU: R71.2, U4.133 (PTD6/LLWU_P15/ADC0_SE7B)
TPS: C14.1, D9.A, D10.C, R44.2, R118.2
TPS_CPU: U3.13 (-IN), U3.14 (OUT), U4.81 (PTB0/LLWU_P5/ADC0_SE8/ADC1_SE8)
TPS_SIGNAL: C13.1, J4.20, R44.1
TX5: J4.4, U4.45 (PTE24/ADC0_SE17)
TX_CPU: J3.16, U4.96 (PTB17)
USBD_N: R58.2, U4.20 (USB0_DM)
USBD_P: R39.2, U4.19 (USB0_DP)
VDDA: C39.1, FL3.1, R19.2, U4.31 (VDDA)
VIN: J4.34, U$18.1, U$18.2, U$18.6, U$18.7
VOUT33: U4.21 (VOUT33)
VR1+: J3.8, R25.2, R29.1
VR1-: J3.6, R26.2, R29.2
VR2+: J4.24, R27.2, R32.2
VR2-: J4.6, R32.1, R56.2
VREFL: C35.1, C38.1, U4.33 (VREFL), U4.34 (VSSA)

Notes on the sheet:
INJECTOR 1
INJECTOR 2
INJECTOR 3
INJECTOR 4
BOOST
IDLE
GENERIC OUT1 - HIGH CURRENT
GENERIC OUT2 - HIGH CURRENT
O2 SENSOR
STEPPER DRIVER
SB ECU 1.0
Designed for Speeduino firmware
08/14/2020
SB Toonz
www.sbtoonz.com
IAT / INLET AIR TEMPERATURE SENSOR
CLT / COOLANT TEMPERATURE SENSOR
TPS / THROTTLE POSITION SENSOR
MAP SENSOR
BRV / BATTERY REFERENCE VOLTAGE
RESET PROTECTION
CRANK AND CAM SENSORS
IGNITION
CAN
O2_2 SENSOR
FUEL PUMP
FAN
LC1
CLUTCH CONTROL
TACHOMETER
INJECTOR 5
INJECTOR 6
INJECTOR 7
INJECTOR 8
LOGIC LEVEL CONVERTER
POWER SUPPLY 5V 3A MAX. + 3V3 0.8A MAX.
BATTERY REVERSE PROTECTION
LOGIC CONVERTERS

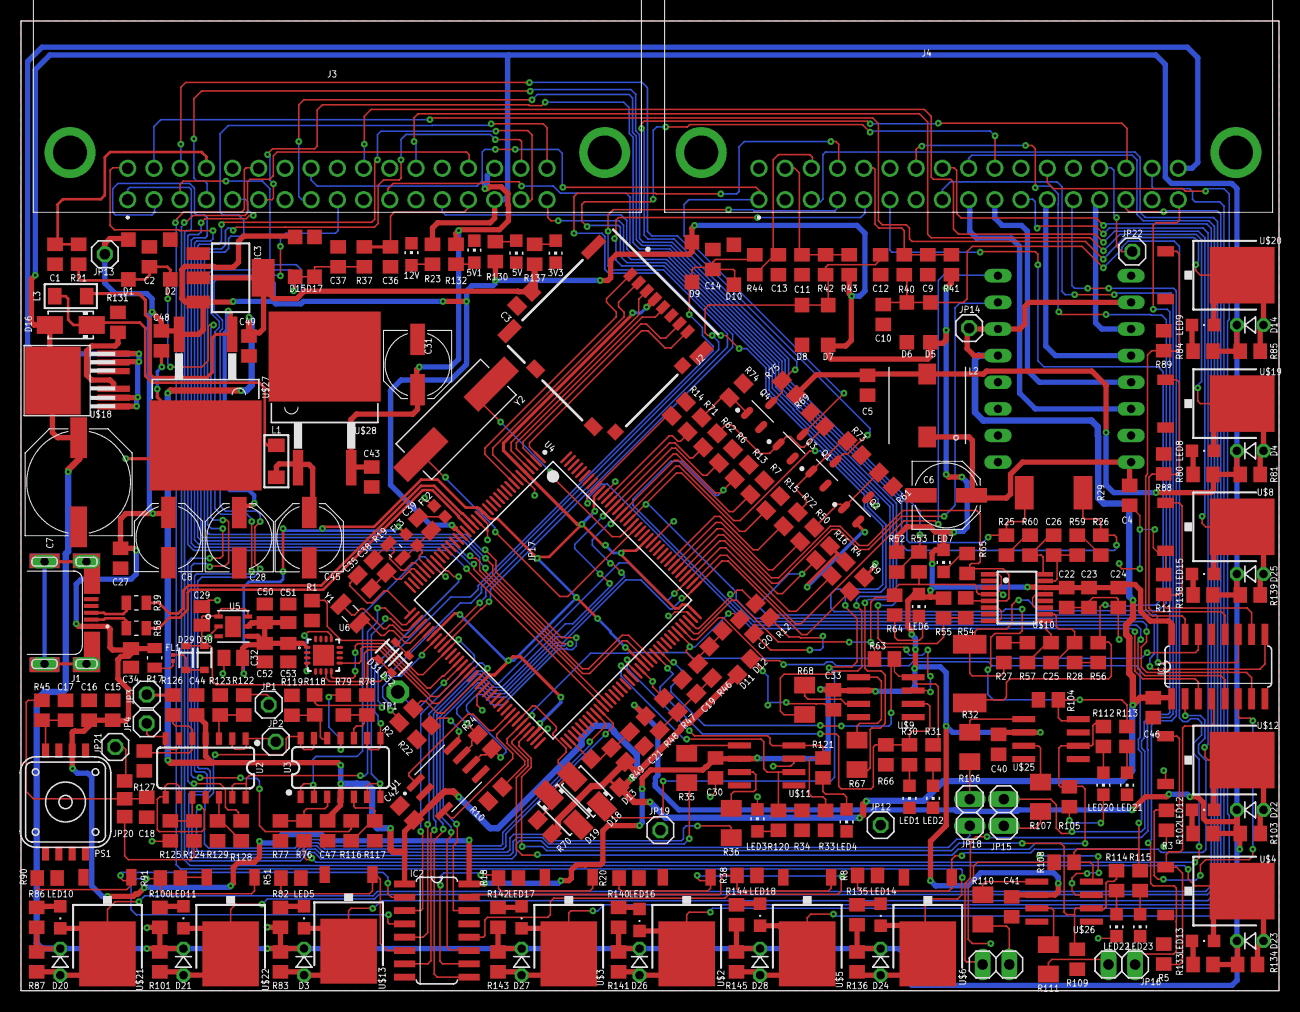
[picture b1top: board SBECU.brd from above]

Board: 2 copper layers, 120.0 x 92.5 mm, 311 parts (0 on the bottom side), 214 nets.

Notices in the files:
parts and their libraries:
rc-master-smd: Copyright (C) 2007, Bob Starr
Wurth Passive: Copyright: Würth Elektronik
SparkFun-IC-Amplifiers: Licensing: Creative Commons ShareAlike 4.0 International - https://creativecommons.org/licenses/by-sa/4.0
